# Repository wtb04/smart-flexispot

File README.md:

<h1 align="center">Smart Flexispot</h1>

<p align="center">
  A room controller that took the place of my standing desk's keypad.
</p>

<p align="center">

</p>

<p align="center">
  <a href="#a-tour">A tour</a> |
  <a href="docs/getting-started.md">Getting started</a> |
  <a href="#try-it-without-the-hardware">Simulator</a> |
  <a href="docs/how-it-works.md">How it works</a> |
  <a href="CHANGELOG.md">Changelog</a>
</p>

Smart Flexispot is firmware for an [M5Stack Tab5](https://docs.m5stack.com/en/core/Tab5) that sits on my desk and drives the Flexispot under it. It replaces the desk's own keypad and controls the room from there: the lights and the heating through Home Assistant, and the desk itself. Along the way it also picked up what is playing on Jellyfin, my timetable with when to leave for it, the planes going over, and a focus timer.

> [!NOTE]
> It is built around my desk, my room, my Home Assistant, my calendars and my phone, so a lot of it only makes sense in my setup. Treat it as a demo of what a desk panel can do and take whatever ideas or pieces are useful. Getting it running for yourself will mean changing things.

> [!NOTE]
> Most of the code was written with AI rather than by hand, so it shows less of my coding skills (if those still count for much nowadays) and more of how I think using something like this should feel. It is also just a fun project for myself, and building it this way made it a matter of weeks instead of months.

Issues are welcome; for pull requests, expect slow answers, as this is a project for my own desk.

I am not affiliated with, or endorsed by, any of the products or services named here: Flexispot, LoctekMotion, M5Stack, Espressif, Home Assistant, Jellyfin, Anthropic, Planespotters or the flight and weather data sites. Their names are trademarks of their owners.

## Highlights

- The lights, the heating and the air from Home Assistant, and the panel itself shows up in Home Assistant over MQTT.
- The desk's height, Stand and Sit, and six presets instead of the control box's four, over a cable or over Bluetooth.
- What plays on Jellyfin, with a cinema view that has the lights and the desk within reach.
- A live radar of the planes overhead: who is flying, where to, their photo and their trail.
- The next lecture, a countdown, and when to leave to get there on time.
- Desk Link, a small app that connects my laptops to the panel, on macOS and on Linux: what plays there shows on the panel and is steered from it, Claude Code's sessions come through it, and the desk goes to Stand or Sit from the laptop.
- A presentation clicker: Next and Back over the whole screen for slides on the laptop, with the page of how many in Okular or Preview, the time, and the file full screen.
- A pill in the bar while a Claude Code session on a laptop works, amber when one waits on you.
- A focus timer, a presence sensor from your phone, and diagnostics for every part, on the panel itself.
- A simulator that runs the real UI on a Mac, and host tests with coverage in CI.

## Why

I wanted one place to control my room from, mostly the lights and the heating. The spot where the desk's keypad sat, right at the edge of the desk, turned out to be the perfect place for it. Then I found [LoctekMotion_IoT](https://github.com/iMicknl/LoctekMotion_IoT), which works out what the control box and its keypad say to each other, so I could build my own controller and replace the keypad entirely.

Once the screen was there, the extra features kept coming, each one making it a bit more useful: what is playing, when to leave for the next lecture, what that plane is, a timer for focusing.

## A tour

### The home page

What the panel shows most of the day. The dock at the side holds the desk: its height and one button for Stand and Sit, then Home, Calendar and Radar, and the focus timer at its foot. The bar along the top holds what gets touched every day: the time with the Wi-Fi and the phone, the lights and the heating, and what is playing, each opening a card when tapped. Home itself is for looking at: the weather, what comes next, the aircraft overhead and the air. The weather is [Open-Meteo](https://open-meteo.com)'s forecast for home, with the next two hours of rain from [Buienradar](https://www.buienradar.nl) and KNMI's warnings through [MeteoAlarm](https://meteoalarm.org).

### The room

It is built Home Assistant first: every light and thermostat is one of its entities, and every tap goes back to it. The other way round, the panel is a device in Home Assistant over MQTT, so automations can move the desk, turn the screen off or put a message on it, such as the washing machine being done.

### The desk

One button goes between Stand and Sit, showing which way while the desk moves, and a tap on the height folds out up, down and the other presets. There are six presets instead of the control box's four, the desk is [wired straight to the Tab5 or reached over Bluetooth](#connecting-the-desk), and it is safe by default: a move from Home Assistant stops unless it keeps being asked for, and the byte that would factory-reset the box is pinned by a test.

### Films and series

When something plays on Jellyfin the bar follows it, and holding it there sends the desk to its viewing height. The cinema view has the episode's still, when it ends, skip intro, next episode, ten seconds back and on, subtitles and volume, with the lights and the desk within reach. A swipe across the picture goes to the episode before or after. Only what the player playing would act on is shown.

### The laptop

[Desk Link](desklink/), a small app in the menu bar on my Mac ([macOS](desklink/macos/)) and in the bar on Linux ([Linux](desklink/linux/), any MPRIS player), connects a laptop to the panel. Whatever plays there shows on the panel with its cover, a video in the cinema view and music on the media card, and the panel's buttons pause, seek, skip and change the volume there. Claude Code's sessions come through it too, and the desk goes to Stand or Sit from its menu, with its height. With a PDF open in Okular, or in Preview on the Mac, the laptop's mark in the panel's bar lights up and opens a presentation clicker: Next and Back over the whole screen as Page Down and Page Up, held to go faster, with which page of how many, the time on the slide and in all, and a button to show the file full screen. The speaker comes first, then Jellyfin, then the laptop, and whatever plays before whatever is paused. Everything the two send each other is encrypted with a key they share, and each regularly checks that the other is still there.

<p align="center"><picture><source media="(prefers-color-scheme: dark)" srcset="desklink/macos/shots/menu-dark.png"></picture></p>

### Planes overhead

| On Home | The radar page |
|---|---|
|  |  |

Purely because it's fun: everything flying within 20 to 160 km on a map of the coast, each plane coloured by its height, with its airline, route, photo and trail. Left alone it follows the most notable aircraft in view, an A380 over a 737, taking turns every few minutes. Positions come from [adsb.lol](https://adsb.lol) and [adsb.fi](https://adsb.fi), aircraft and routes from [adsbdb](https://www.adsbdb.com) and [hexdb.io](https://hexdb.io), photos from [Planespotters](https://www.planespotters.net). adsb.fi's data is for personal, non-commercial use only, and so is anything built on it here.

### The day

The next thing on my iCal feeds (mine come from [CalendarChanger](https://github.com/wtb04/CalendarChanger)) with a countdown, and with a journey planner, when to leave: every leg by bike, train, bus or on foot, with delays as they come in.

### Focus

| Focus | Fullscreen |
|---|---|
|  |  |

A focus timer in rounds, 25 minutes on and 5 off by default, from its button at the dock's foot, and fullscreen from there.

### Claude Code

| Working | Waiting on you |
|---|---|
|  |  |

While a Claude Code session on one of my laptops works, a pill in the bar shows it, turning amber with a chime when one waits for me to allow something; tapped, it shows each session's project, steps and what it did last. With many at once, Desk Link's settings keep them showing without the chime and the notice. The laptops tell the panel through Claude Code's hooks and Desk Link, sealed, and only names leave them, never a prompt, a reply or a file's contents.

### Away from the desk

The panel knows my phone over Bluetooth. While it is away, the personal pages are hidden and the extra presets show for whoever uses the desk then. While the screen is off, the panel fetches nothing that only the screen would show.

### Setup and diagnostics

| Setup | Diagnostics |
|---|---|
|  |  |

Setup is a sidebar: Screen and sound for the brightness, the dark or light look and the accent colour; Focus for its lengths; Panel for which way up it hangs, whether the personal pages hide while I am away, charging, and the desk by cable or Bluetooth; System for updates and restarting; and Diagnostics, every part with its state and a log, so when something is off you can see why without a laptop.

## Will it work with my desk?

Probably, if the control box speaks the HS01B / HS13B dialect, which most LoctekMotion boxes (and so most Flexispots) do. The HCB2xx series does not.

The protocol and pinouts come from [iMicknl/LoctekMotion_IoT](https://github.com/iMicknl/LoctekMotion_IoT), which did the hard work of figuring out what the control box says. If your box is not covered there, it will not work here either.

## Connecting the desk

<picture>
  <source media="(prefers-color-scheme: dark)" srcset="docs/diagrams/overview-dark.svg">
  
</picture>

The panel takes the keypad's place on the control box's RJ45 line, in one of two ways:

- **A cable to the Tab5.** Four wires from the line to the Tab5's M5-Bus, and nothing else to build. The panel stays where the cable reaches.
- **Over Bluetooth, with a companion.** A small ESP32 stays on the line at the desk and the panel talks to it, so the panel can go anywhere in the room on its battery, and updates the companion over the air too.

The companion is an ESP32 DevKit on a carrier board of my own: powered by the desk, shifting the box's 5 V signal down for the ESP32, with two LEDs in its RJ45 jack for the Bluetooth and desk links.

| Top | Bottom |
|---|---|
|  |  |

The KiCad project and everything to have it made are in [pcb/](pcb/), and the wiring for both ways in [getting started](docs/getting-started.md#2-connect-the-desk).

## Getting started

The hardware, wiring the desk directly or through the companion, ESP-IDF, the secrets, flashing and updating over Wi-Fi, and connecting Claude Code on your laptops are all in [docs/getting-started.md](docs/getting-started.md).

## Try it without the hardware

The simulator runs the panel's own UI in a window on your Mac, with the desk, Home Assistant and Jellyfin played by stubs you drive from the keyboard:

```sh
sim/run.sh
```

The calendar, journey and radar are real, and those are the only things it is allowed to reach, so it can never move a real desk or turn off your lights. All screenshots here are from it. See [sim/README.md](sim/README.md) for the keys.

## How it works

How the panel is put together inside, the desk protocol, and how to run the tests, the simulator and the development build are in [docs/how-it-works.md](docs/how-it-works.md).

## Credits

- [iMicknl/LoctekMotion_IoT](https://github.com/iMicknl/LoctekMotion_IoT) for working out the control box protocol and pinouts. This project would not exist without it.
- [adsb.lol](https://adsb.lol), [adsb.fi](https://adsb.fi), [adsbdb](https://www.adsbdb.com), [hexdb.io](https://hexdb.io) and [Planespotters](https://www.planespotters.net) for the planes, and the photographers for their photos.
- [Open-Meteo](https://open-meteo.com), [Buienradar](https://www.buienradar.nl), and KNMI through [MeteoAlarm](https://meteoalarm.org), for the weather.
- [Natural Earth](https://www.naturalearthdata.com) for the map.
- [ungive/mediaremote-adapter](https://github.com/ungive/mediaremote-adapter), through which Desk Link reads macOS's Now Playing.

## Licence

Copyright 2026 Wouter ten Brinke. The code, the documents and the board are under the Apache License 2.0, see [LICENSE](LICENSE) and [NOTICE](NOTICE). What comes from others keeps its own licence, listed in [THIRD_PARTY_NOTICES.md](THIRD_PARTY_NOTICES.md); the aircraft photos in the screenshots are their photographers'.

Made by [Wouter ten Brinke](https://woutertenbrinke.nl), with a [write-up of the project](https://woutertenbrinke.nl/projects/smart-flexispot) on my site.

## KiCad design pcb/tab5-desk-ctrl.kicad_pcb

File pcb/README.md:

# Desk companion board

A carrier for an ESP32 DevKit V1 (30-pin) that plugs into a LoctekMotion / Flexispot control box over RJ45. It runs off the desk's 5 V, shifts the box's 5 V signal down for the ESP32, and uses the jack's two LEDs for Bluetooth (`BT`) and the desk link (`LINK`). What they show is in [getting started](../docs/getting-started.md#option-2-over-bluetooth-with-a-companion). The firmware is in [`../proxy`](../proxy).

| | |
|---|---|
|  |  |
|  |  |
|  |  |

Rev2, 80 × 35.2 mm, two layers, 4 × M3. The schematic is also a [PDF](fab/tab5-desk-ctrl-schematic.pdf).

## Wiring

| RJ45 pin | Control box | On the board | ESP32 |
|---|---|---|---|
| 8 | 5 V | PTC fuse, SS14 diode, 470 µF | VIN |
| 7 | GND | ground pour | GND |
| 6 | box RX | 220 Ω | GPIO17 (TX2) |
| 5 | box TX, 5 V | 10k / 15k divider, BAT54S clamp | GPIO16 (RX2) |
| 4 | wake ("PIN 20") | 220 Ω | GPIO23 |
| 12 / 11 | LED | 220 Ω | GPIO32, `BT` |
| 10 / 9 | LED | 220 Ω | GPIO33, `LINK` |

This is how my control box uses pins 4 to 8: it sends on pin 5 and listens on pin 6, as the published LoctekMotion tables have it. Measure yours before plugging it in. The back of the board names what you probe there: the jack's pin numbers beside its pads with what each carries, `BT` and `LINK` by the LED pads, C3's + side, and the DevKit's pin names along both sockets, as on the top.

The companion firmware's defaults are this board's: TX on GPIO17, RX on GPIO16, wake on GPIO23.

## Ordering

Upload `fab/tab5-desk-ctrl-gerbers.zip`, `-bom.csv` and `-cpl.csv` to JLCPCB with SMT assembly on the top side. The jack, the two headers and C3 are hand-soldered, see `fab/tab5-desk-ctrl-hand-solder.csv`. Print `fab/tab5-desk-ctrl-check-1to1.pdf` at 100 % and hold the jack and the DevKit against it before you order.

## Files

The KiCad files are generated by the Python scripts here, so change the scripts rather than the board. `make_fab.sh` builds everything in `fab/`, and `render.sh` the pictures in `img/`. The scripts look for KiCad 9 where macOS puts it; `KICAD9_FOOTPRINT_DIR`, `KICAD9_SYMBOL_DIR` and `KICAD_CLI` point them elsewhere. The jack is LCSC part [C386757](https://www.lcsc.com/product-detail/C386757.html), where its datasheet is; its 3D model in `3dmodels/` is LCSC's.

## Things to know

- **Only for a box with 5 V on pin 8.** Nothing on the board protects against more: a LoctekMotion variant with about 29 V there destroys the capacitors, the DevKit's regulator and probably the ESP32.
- **C3 has a + side.** It is the 470 µF electrolytic behind the jack, 10 V or more, 8 mm across and no taller than 11.5 mm, its long leg in the pad marked +. It is optional: the companion also starts without it, with one restart at power-up. It carries the radio's start-up surge: on desk power alone, rev1 browned out and restarted at every boot.
- **Rev1 had pins 5 and 6 the other way round.** On a rev1 board the companion needs TX on GPIO16 and RX on GPIO17, in `proxy/sdkconfig`, and R1 bridged, since commands to the box cannot pass its 10k. GPIO17 then takes the box's 5 V through 220 Ω, which is outside the ESP32's ratings.
- **The diode has to be a BAT54S.** The BAT54A and BAT54C come in the same package and both break RX without a sound: one holds the line near 0.6 V, the other keeps its low near 2.7 V. With the box idle, GPIO16 should read about 3.1 V.
- **Use flux made for electronics.** Acid flux for plumbing, such as S-39, leaves a residue that conducts: on a rev1 board it leaked about 6 kΩ from pin 6 to ground and held the box's signal down.
- **R2 is 15k.** The box's TX measured between 5.01 and 5.17 V; 10k over 15k puts that at 3.0 to 3.1 V, inside the ESP32's 3.3 V with room either side, whichever of those it is.
- **Pick the soldermask, silkscreen and finish on the order form.** JLCPCB does not read them from the files.
- **The LED polarity is from the jack's datasheet, not measured.** A LED that stays dark is the wrong way round, which does it no harm. At start-up the companion blinks `BT` twice, `LINK` twice, then both.

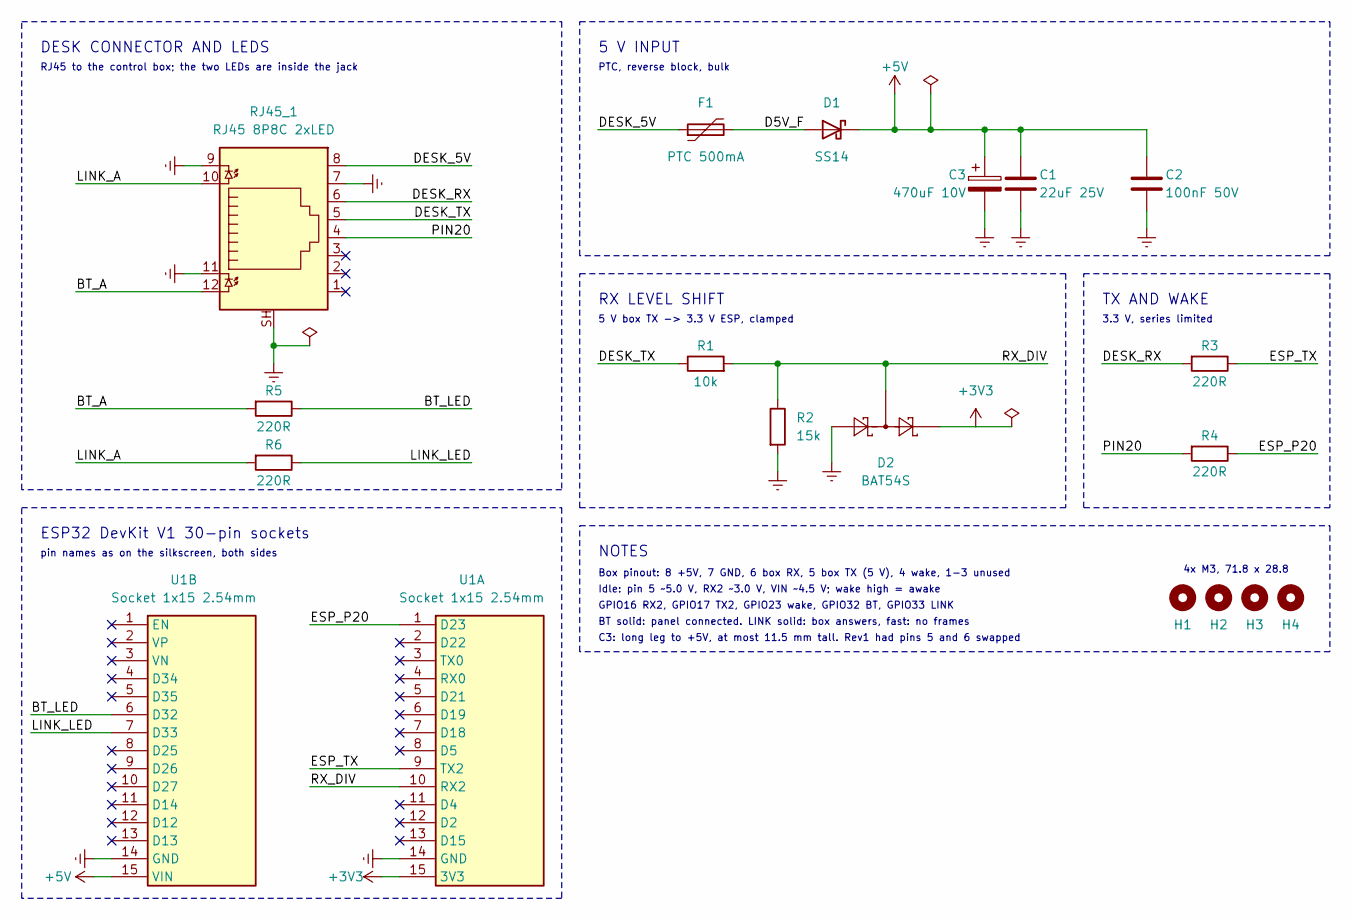
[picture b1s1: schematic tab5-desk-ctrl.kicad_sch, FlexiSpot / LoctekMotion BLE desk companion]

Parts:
C1: 22uF 25V; C_1206_3216Metric
C2: 100nF 50V; C_0805_2012Metric
C3: 470uF 10V; CP_Radial_D8.0mm_P3.50mm
D1: SS14; D_SMA
D2: BAT54S; SOT-23
F1: PTC 500mA; R_1206_3216Metric
H1, H2, H3, H4: M3; MountingHole_3.2mm_M3
R1: 10k; R_0805_2012Metric
R2: 15k; R_0805_2012Metric
R3, R4, R5, R6: 220R; R_0805_2012Metric
RJ45_1: RJ45 8P8C 2xLED; RJ45_Connfly_DS1128-09-S8xx-S_Horizontal
U1A, U1B: Socket 1x15 2.54mm; PinSocket_1x15_P2.54mm_Vertical

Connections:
+3V3: D2.2 (K), U1A.15 (3V3)
+5V: C1.1, C2.1, C3.1, D1.1 (K), U1B.15 (VIN)
/BT_A: R5.2, RJ45_1.12
/BT_LED: R5.1, U1B.6 (D32)
/D5V_F: D1.2 (A), F1.2
/DESK_5V: F1.1, RJ45_1.8
/DESK_RX: R3.2, RJ45_1.6
/DESK_TX: R1.1, RJ45_1.5
/ESP_P20: R4.1, U1A.1 (D23)
/ESP_TX: R3.1, U1A.9 (TX2)
/LINK_A: R6.2, RJ45_1.10
/LINK_LED: R6.1, U1B.7 (D33)
/PIN20: R4.2, RJ45_1.4
/RX_DIV: D2.3 (COM), R1.2, R2.1, U1A.10 (RX2)
GND: C1.2, C2.2, C3.2, D2.1 (A), R2.2, RJ45_1.7, RJ45_1.9, RJ45_1.11, RJ45_1.SH, U1A.14 (GND), U1B.14 (GND)

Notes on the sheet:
DESK CONNECTOR AND LEDS
RJ45 to the control box; the two LEDs are inside the jack
5 V INPUT
PTC, reverse block, bulk
RX LEVEL SHIFT
5 V box TX -> 3.3 V ESP, clamped
TX AND WAKE
3.3 V, series limited
ESP32 DevKit V1 30-pin sockets
pin names as on the silkscreen, both sides
NOTES
Box pinout: 8 +5V, 7 GND, 6 box RX, 5 box TX (5 V), 4 wake, 1-3 unused
Idle: pin 5 ~5.0 V, RX2 ~3.0 V, VIN ~4.5 V; wake high = awake
GPIO16 RX2, GPIO17 TX2, GPIO23 wake, GPIO32 BT, GPIO33 LINK
BT solid: panel connected. LINK solid: box answers, fast: no frames
C3: long leg to +5V, at most 11.5 mm tall. Rev1 had pins 5 and 6 swapped
4x M3, 71.8 x 28.8

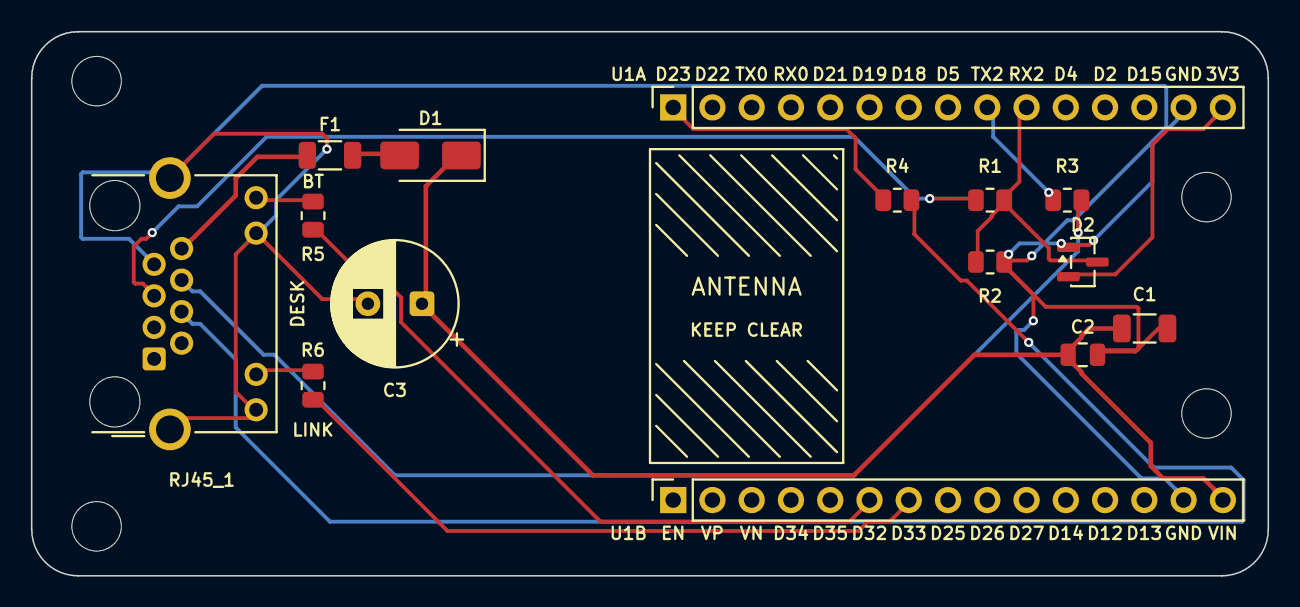
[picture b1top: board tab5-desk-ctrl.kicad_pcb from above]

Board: 2 copper layers, 80.0 x 35.2 mm, 19 parts (0 on the bottom side), 15 nets.

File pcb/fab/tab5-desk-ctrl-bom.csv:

Comment,Designator,Footprint,JLCPCB Part #（optional）
22uF 25V,C1,Capacitor_SMD:C_1206_3216Metric,C12891
100nF 50V,C2,Capacitor_SMD:C_0805_2012Metric,C49678
SS14,D1,Diode_SMD:D_SMA,C2480
BAT54S,D2,Package_TO_SOT_SMD:SOT-23,C7420333
PTC 500mA,F1,Resistor_SMD:R_1206_3216Metric,C106264
10k,R1,Resistor_SMD:R_0805_2012Metric,C17414
15k,R2,Resistor_SMD:R_0805_2012Metric,C17475
220R,"R3,R4,R5,R6",Resistor_SMD:R_0805_2012Metric,C17557

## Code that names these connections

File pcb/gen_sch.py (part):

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        LABELS.append((net, x, a[1], 0 if x < a[0] else 180))

# --- DESK CONNECTOR AND LEDS: signals right, LEDs left, grounds at the pin ---
for p, net in (("8","DESK_5V"), ("6","DESK_RX"), ("5","DESK_TX"), ("4","PIN20")):
    stub("RJ45_1", p, 76.20, net)
stub("RJ45_1", "7", 60.96)                                     # GND, pointing right
# Datasheet (both the PC-board-layout and the bottom view) marks the four LED
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stub("RJ45_1", "11", 35.56)
w(P("RJ45_1","SH"), (48.26, 60.96))                            # shield to GND
w((48.26, 58.42), (53.34, 58.42))                              # and its PWR_FLAG
for r, anode, gpio in (("R5","BT_A","BT_LED"), ("R6","LINK_A","LINK_LED")):
    stub(r, "2", 20.32, anode)
    stub(r, "1", 76.20, gpio)

# --- 5 V INPUT ------------------------------------------------------------
stub("F1", "1", 93.98, "DESK_5V")
w(P("F1","2"), P("D1","2"))
LABELS.append(("D5V_F", *P("D1","2"), 180))
w(P("D1","1"), (171.45, 27.94))                                # +5V rail
w((135.89, 22.86), (135.89, 27.94))                            # +5V symbol
w((140.97, 22.86), (140.97, 27.94))                            # PWR_FLAG
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w((147.32, 69.85), (152.40, 69.85))                            # and its flag

# --- TX AND WAKE ----------------------------------------------------------
for r, desk, esp in (("R3","DESK_RX","ESP_TX"), ("R4","PIN20","ESP_P20")):
    stub(r, "2", 165.10, desk)
    stub(r, "1", 195.58, esp)

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    if touching >= 3:
        sch.junctions.append(Junction(position=Position(*p),uuid=str(uuid.uuid4())))

# Plain labels: on the root sheet KiCad names these nets "/DESK_TX", and
# gen_pcb.py gives the board's nets the same names.
for t,x,y,a in LABELS:
    just = Justify(horizontally="right" if a in (180, 270) else "left", vertically="bottom")
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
